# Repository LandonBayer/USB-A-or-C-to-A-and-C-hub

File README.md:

# USB-A-or-C-to-A-and-C-hub
Hack Club upload

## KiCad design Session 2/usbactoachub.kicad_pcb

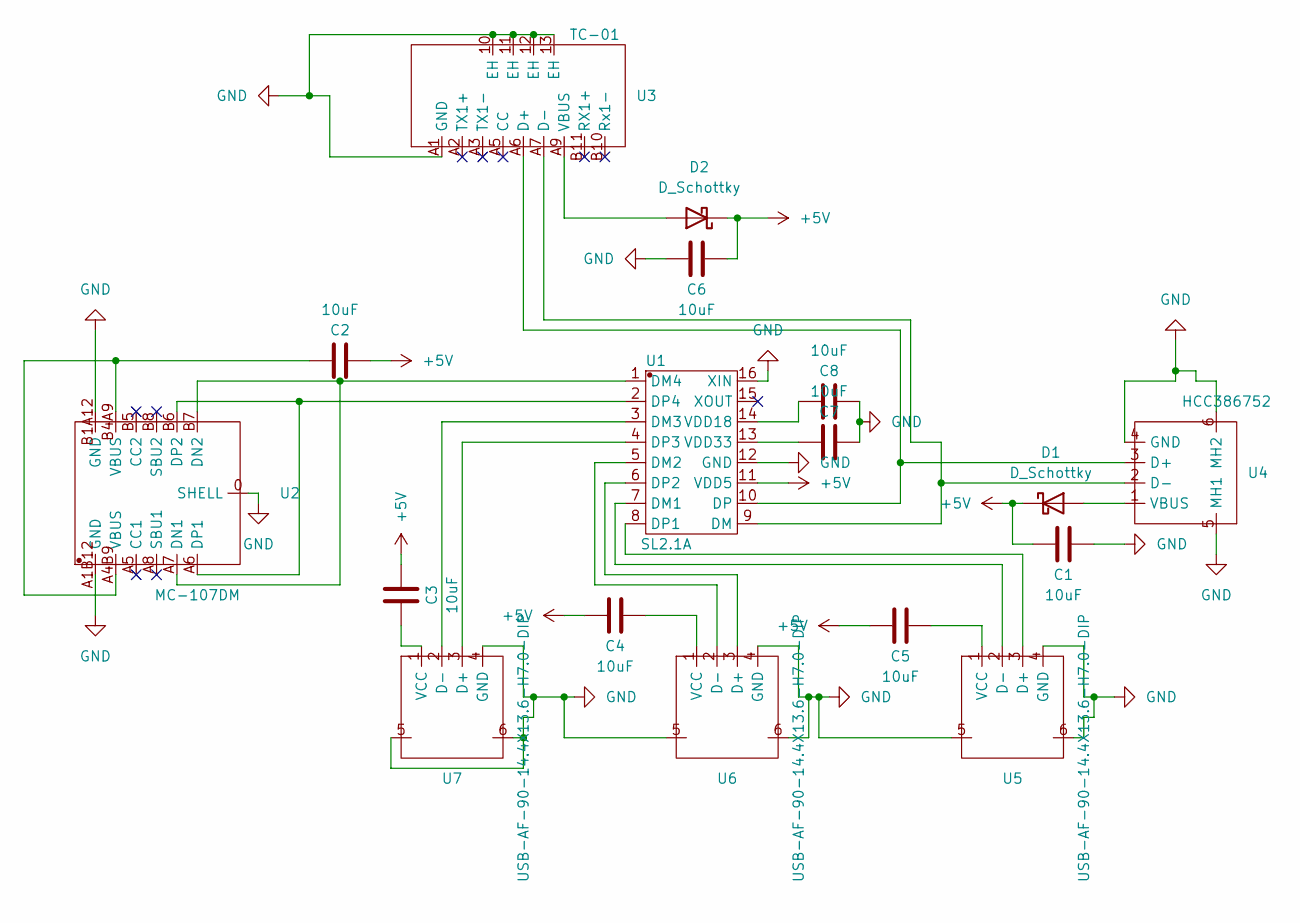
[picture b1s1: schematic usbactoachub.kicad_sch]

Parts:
C1, C2, C3, C4, C5, C6, C7, C8: 10uF; C0603
D1, D2: D_Schottky; SOD-323_L1.8-W1.3-LS2.5-RD
U1: SL2.1A; SOP-16_L10.0-W3.9-P1.27-LS6.0-BL
U2: MC-107DM; USB-C-SMD_MC-107DM
U3: TC-01; USB-C-SMD_TYPE-C-9PIN-TC-01
U4: HCC386752; USB-SMD_KH-USB-AM-4P-CB_FIXED
U5, U6, U7: USB-AF-90-14.4X13.6-H7.0-DIP; USB-A-TH_C46407

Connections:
+5V: C1.2, C2.2, C3.1, C4.2, C5.2, C6.1, D1.1 (K), D2.1 (K), U1.11 (VDD5)
GND: C1.1, C6.2, C7.2, C8.2, U1.12 (GND), U1.16 (XIN), U2.0 (SHELL), U2.A1B12 (GND), U2.B1A12 (GND), U3.10 (EH), U3.11 (EH), U3.12 (EH), U3.13 (EH), U3.A1 (GND), U4.4 (GND), U4.5 (MH1), U4.6 (MH2), U5.4 (GND), U5.5, U5.6, U6.4 (GND), U6.5, U6.6, U7.4 (GND), U7.5, U7.6
unnamed: C2.1, U2.A4B9 (VBUS), U2.B4A9 (VBUS)
unnamed: D1.2 (A), U4.1 (VBUS)
unnamed: D2.2 (A), U3.A9 (VBUS)
unnamed: U1.7 (DM1), U5.2 (D-)
unnamed: U1.5 (DM2), U6.2 (D-)
unnamed: U1.3 (DM3), U7.2 (D-)
unnamed: U1.1 (DM4), U2.A7 (DN1), U2.B7 (DN2)
unnamed: U1.9 (DM), U3.A7 (D-), U4.2 (D-)
unnamed: U1.8 (DP1), U5.3 (D+)
unnamed: U1.6 (DP2), U6.3 (D+)
unnamed: U1.4 (DP3), U7.3 (D+)
unnamed: U1.2 (DP4), U2.A6 (DP1), U2.B6 (DP2)
unnamed: U1.10 (DP), U3.A6 (D+), U4.3 (D+)
unnamed: C8.1, U1.14 (VDD18)
unnamed: C7.1, U1.13 (VDD33)
unnamed: C5.1, U5.1 (VCC)
unnamed: C4.1, U6.1 (VCC)
unnamed: C3.2, U7.1 (VCC)

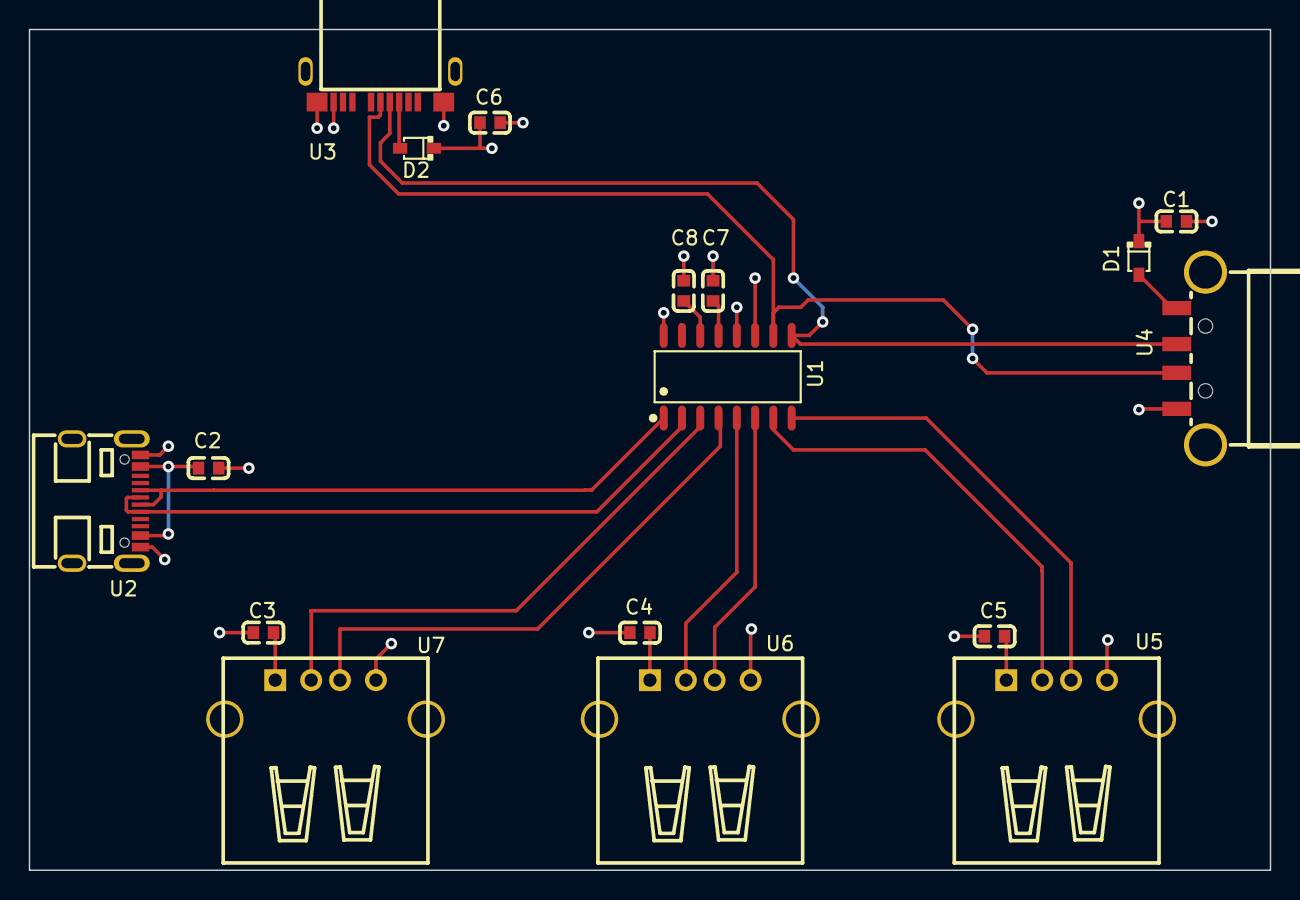
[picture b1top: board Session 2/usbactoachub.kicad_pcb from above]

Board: 4 copper layers, 86.2 x 58.4 mm, 17 parts (0 on the bottom side), 20 nets.

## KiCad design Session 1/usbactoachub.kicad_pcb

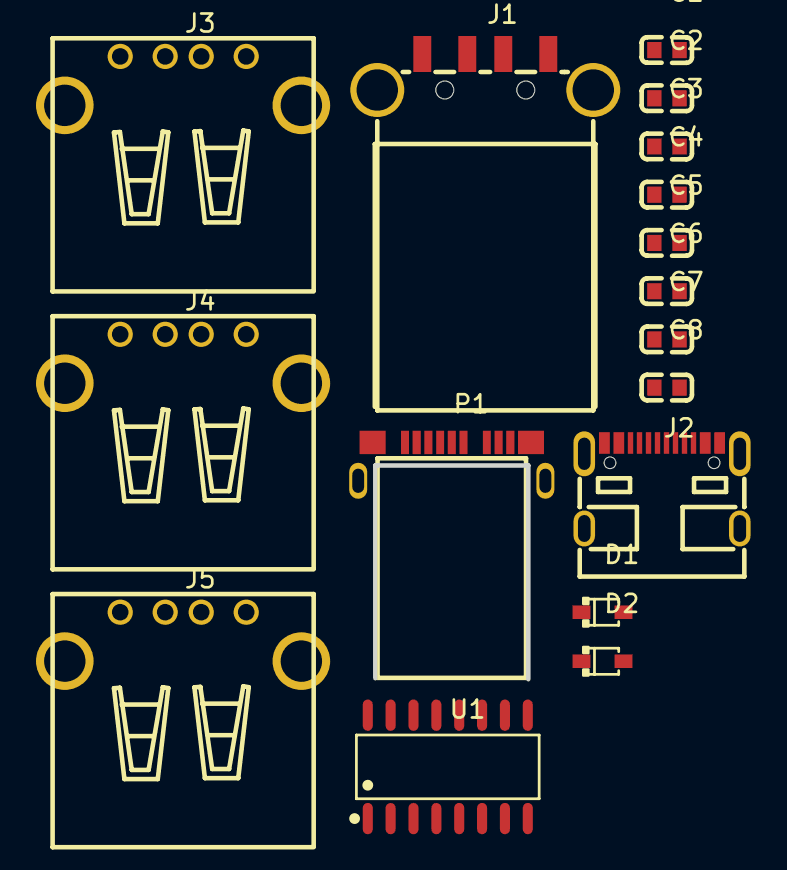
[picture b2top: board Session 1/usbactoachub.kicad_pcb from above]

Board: 2 copper layers, 17 parts (0 on the bottom side), 19 nets, no tracks yet.

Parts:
C1, C2, C3, C4, C5, C6, C7, C8: 10uF; C0603
D1, D2: D_Schottky; SOD-323_L1.8-W1.3-LS2.5-RD
J1: USB_A; USB-SMD_KH-USB-AM-4P-CB_FIXED
J2: USB_C_Receptacle_USB2.0; USB-C-SMD_MC-107DM
J3, J4, J5: USB_A; USB-A-TH_USB-A-F-90
P1: USB_C_Plug_USB2.0; USB-C-SMD_TYPE-C-9PIN-TC-01
U1: SOP-16_L10.0-W3.9-P1.27-LS6.0-BL

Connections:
+5V: C1.2, C2.2, C3.1, C4.2, C5.2, C6.1, D1.1 (K), D2.1 (K), U1.11 (VDD5)
GND: C1.1, C6.2, C7.2, C8.2, J1.4 (GND), J1.5 (Shield), J3.4 (GND), J4.4 (GND), J5.4 (GND), P1.A1 (GND), U1.12 (GND), U1.16 (XIN)
unnamed: D1.2 (A), J1.1 (VBUS)
unnamed: D2.2 (A), P1.A9 (VBUS)
unnamed: J1.3 (D+), P1.A6 (D+), U1.10 (DP)
unnamed: J1.2 (D-), P1.A7 (D-), U1.9 (DM)
unnamed: J3.3 (D+), U1.8 (DP1)
unnamed: J3.2 (D-), U1.7 (DM1)
unnamed: C5.1, J3.1 (VBUS)
unnamed: J4.3 (D+), U1.6 (DP2)
unnamed: J4.2 (D-), U1.5 (DM2)
unnamed: C4.1, J4.1 (VBUS)
unnamed: J5.3 (D+), U1.4 (DP3)
unnamed: J5.2 (D-), U1.3 (DM3)
unnamed: C3.2, J5.1 (VBUS)
unnamed: J2.A7 (D-), J2.B7 (D-), U1.1 (DM4)
unnamed: J2.A6 (D+), J2.B6 (D+), U1.2 (DP4)
unnamed: C8.1, U1.14 (VDD18)
unnamed: C7.1, U1.13 (VDD33)

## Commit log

2024-07-13 Part 2
2024-07-14 Session 3 (done?)
